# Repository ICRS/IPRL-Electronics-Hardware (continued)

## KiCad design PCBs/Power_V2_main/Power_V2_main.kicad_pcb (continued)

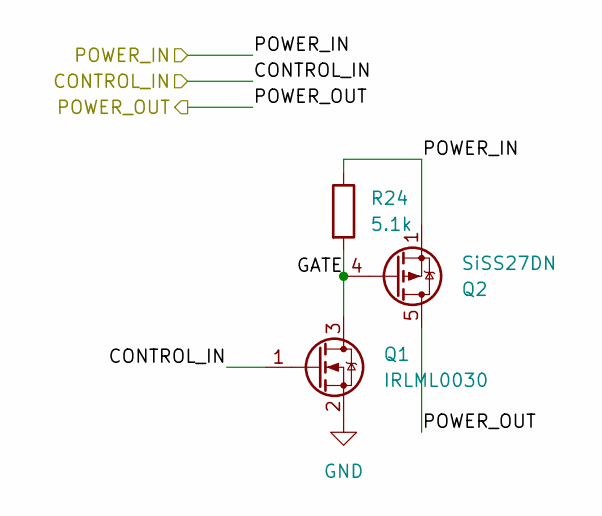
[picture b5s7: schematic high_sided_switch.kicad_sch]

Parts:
Q1: IRLML0030; SOT-23
Q2: SiSS27DN; Vishay_PowerPAK_1212-8_Single
R24: 5.1k; R_0805_2012Metric

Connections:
/14V8_PROTECTED: Q2.1 (S), Q2.2 (S), Q2.3 (S), R24.1; also elsewhere on the board
/Control/IND_GREEN: Q1.1 (G); also elsewhere on the board
/LED Indicators/GREEN_OUT: Q2.5 (D); also elsewhere on the board
/LED Indicators/Green switch/GATE: Q1.3 (D), Q2.4 (G), R24.2
GND: Q1.2 (S); also elsewhere on the board

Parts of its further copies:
Q4, Q7: SiSS27DN; Vishay_PowerPAK_1212-8_Single
Q5, Q6: IRLML0030; SOT-23
R18, R19: 5.1k; R_0805_2012Metric

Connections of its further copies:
/14V8_PROTECTED: Q4.1 (S), Q4.2 (S), Q4.3 (S), Q7.1 (S), Q7.2 (S), Q7.3 (S), R18.1, R19.1; also elsewhere on the board
/Control/IND_SIREN: Q6.1 (G); also elsewhere on the board
/Control/IND_YELLOW: Q5.1 (G); also elsewhere on the board
/LED Indicators/SIREN_OUT: Q7.5 (D); also elsewhere on the board
/LED Indicators/Siren switch/GATE: Q6.3 (D), Q7.4 (G), R19.2
/LED Indicators/YELLOW_OUT: Q4.5 (D); also elsewhere on the board
/LED Indicators/Yellow switch/GATE: Q4.4 (G), Q5.3 (D), R18.2
GND: Q5.2 (S), Q6.2 (S); also elsewhere on the board

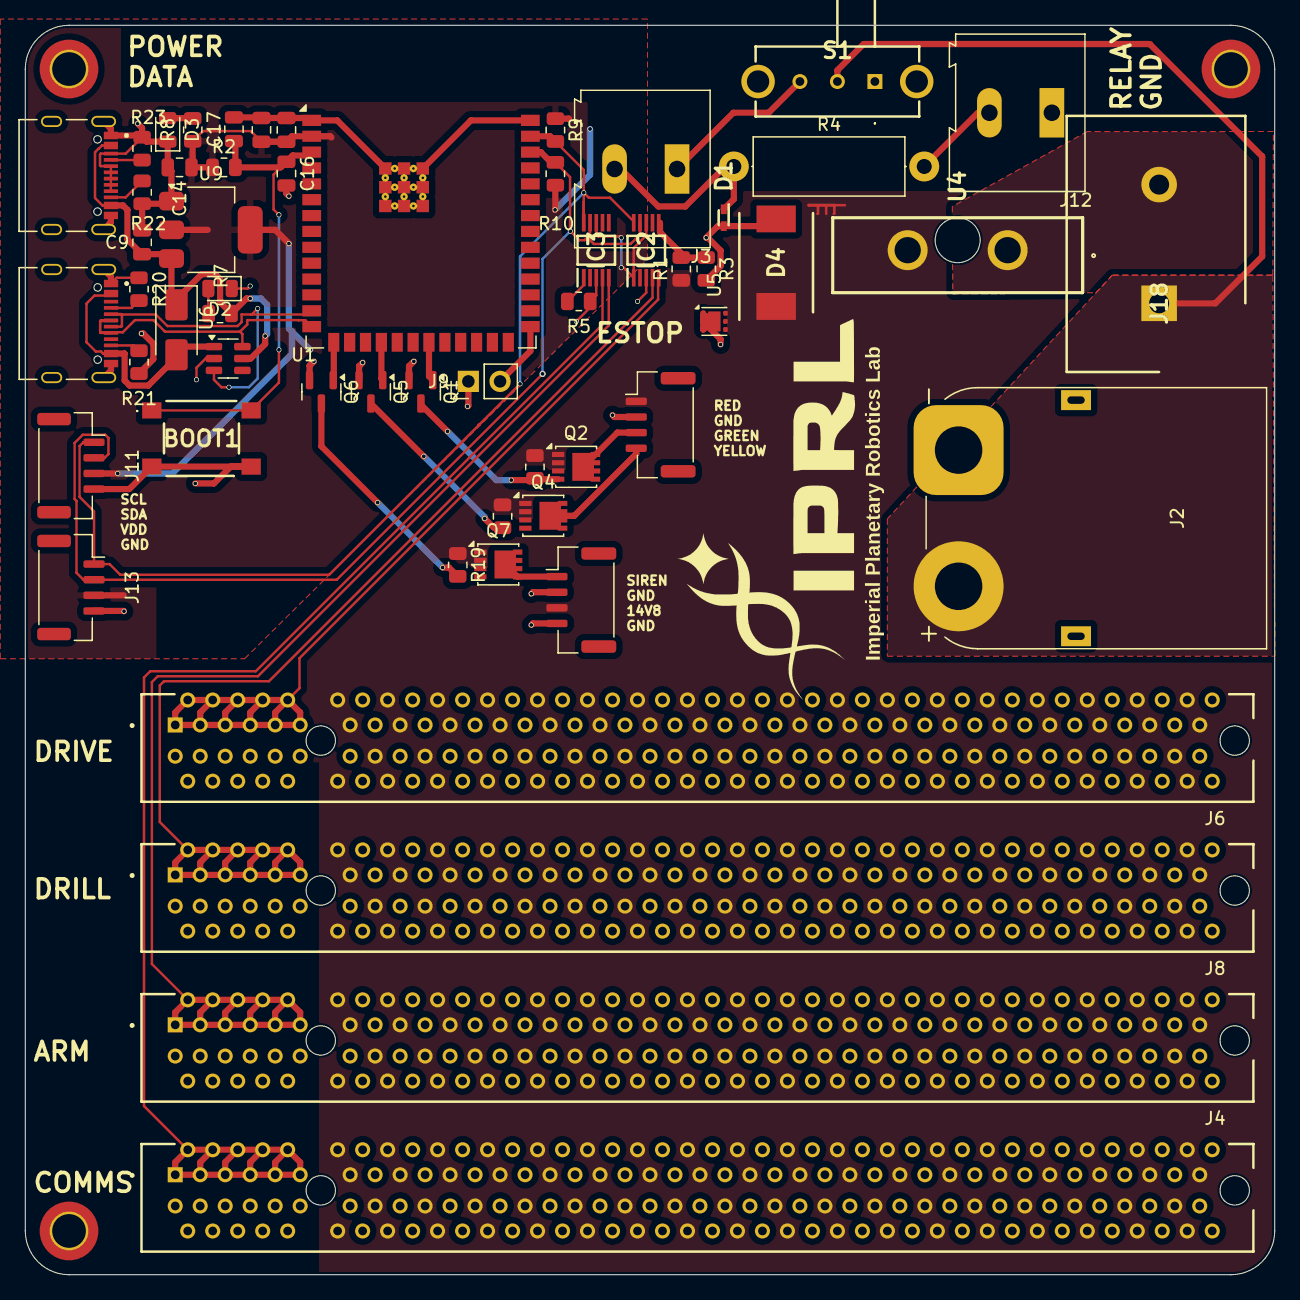
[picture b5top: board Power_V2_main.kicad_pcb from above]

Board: 2 copper layers, 100.0 x 100.0 mm, 60 parts (0 on the bottom side), 37 nets.

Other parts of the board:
J14: Conn_01x04; JST_GH_BM04B-GHS-TBT_1x04-1MP_P1.25mm_Vertical

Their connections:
/14V8_PROTECTED: J14.3; also elsewhere on the board
/LED Indicators/SIREN_OUT: J14.1; also elsewhere on the board
GND: J14.2, J14.4; also elsewhere on the board

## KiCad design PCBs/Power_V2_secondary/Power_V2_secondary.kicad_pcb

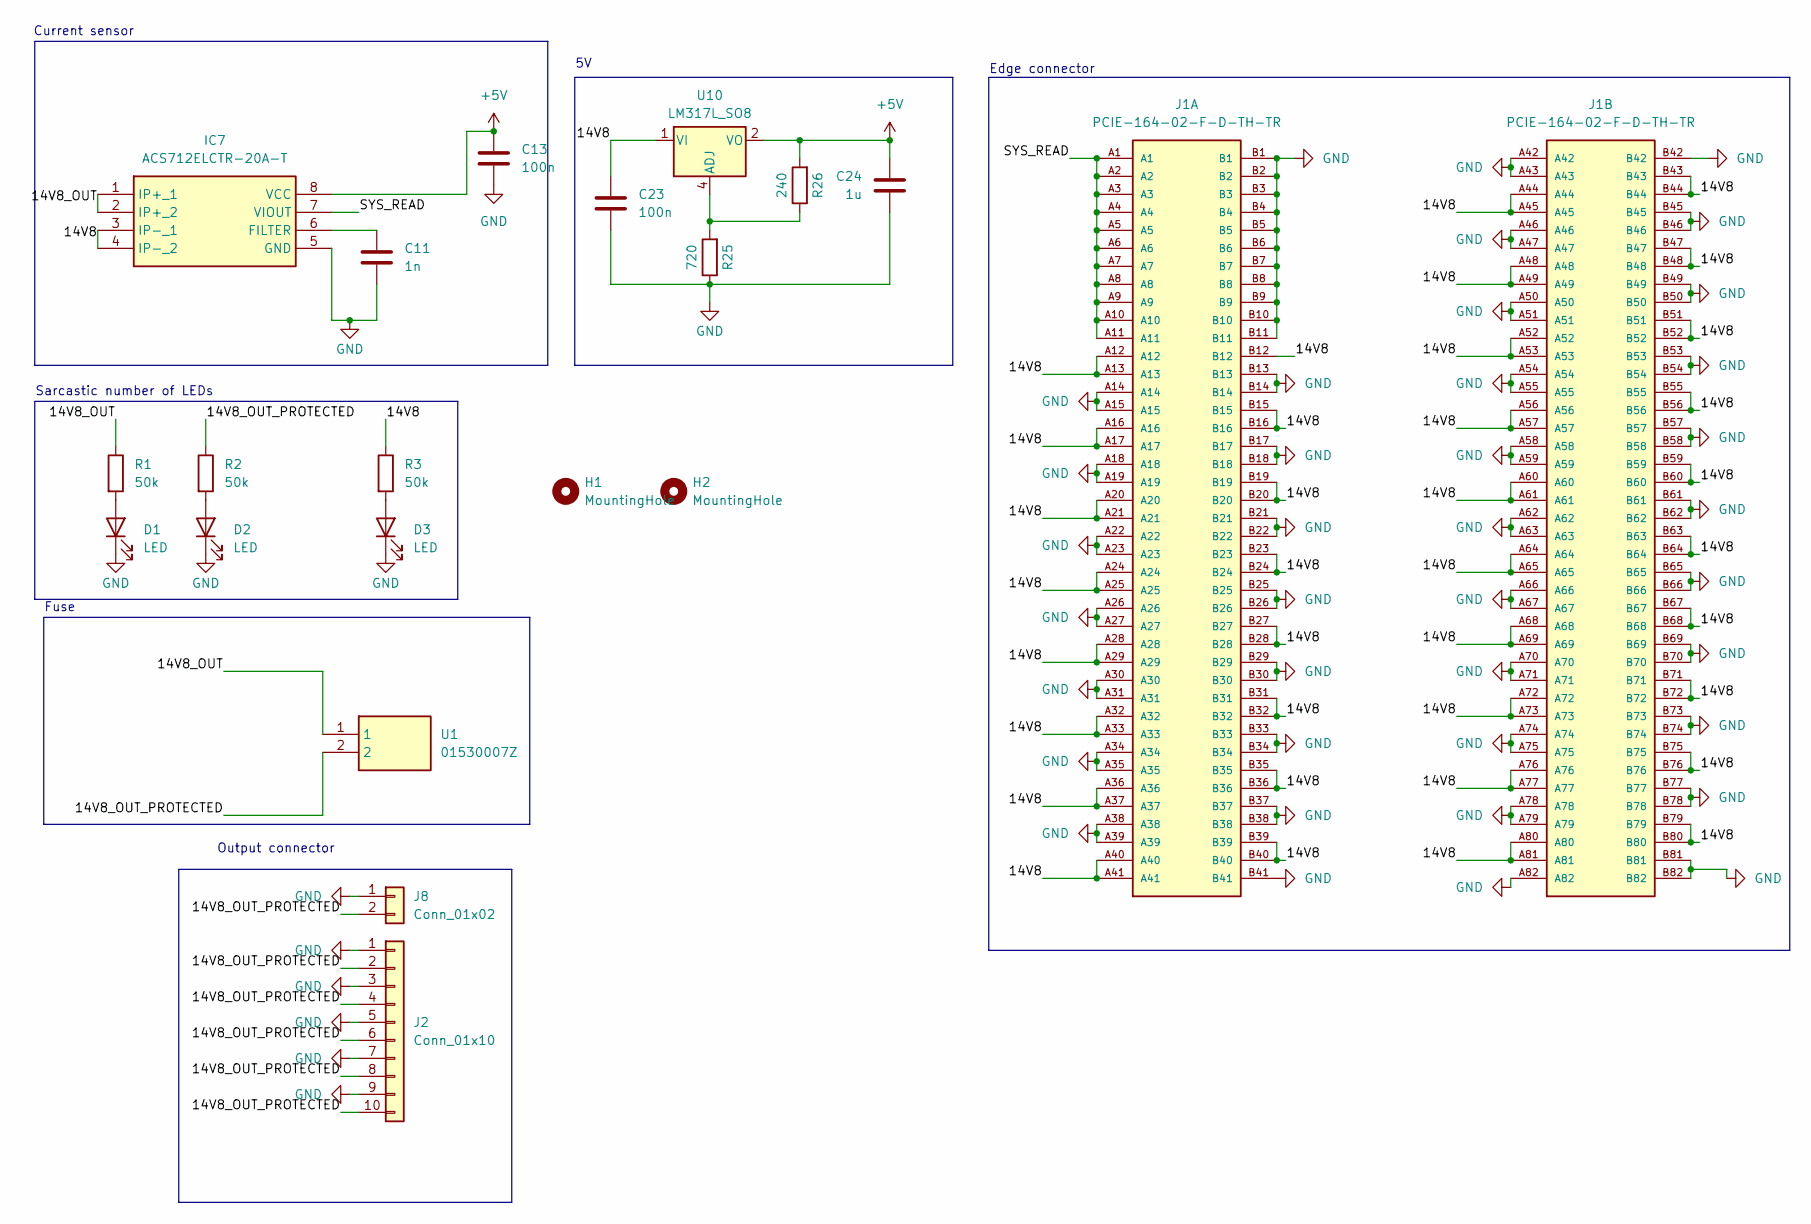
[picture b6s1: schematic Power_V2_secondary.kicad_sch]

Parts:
C11: 1n; C_0805_2012Metric
C13, C23: 100n; C_0805_2012Metric
C24: 1u; C_0805_2012Metric
D1, D2, D3: LED; D_0805_2012Metric
H1, H2: MountingHole; MountingHole_2.7mm_M2.5_DIN965_Pad_TopBottom
IC7: ACS712ELCTR-20A-T; SOIC127P600X175-8N; Manufacturer_Part_Number ACS712ELCTR-20A-T
J1: PCIE-164-02-F-D-TH-TR; BUS_PCIexpress_x16; PARTREV Y
J2: Conn_01x10; TerminalBlock_MaiXu_MX126-5.0-10P_1x10_P5.00mm
J8: Conn_01x02; AMASS_XT60PW-F_1x02_P7.20mm_Horizontal
R1, R2, R3: 50k; R_0805_2012Metric
R25: 720; R_0805_2012Metric
R26: 240; R_0805_2012Metric
U1: 01530007Z; Manufacturer_Part_Number 01530007Z; Mouser Part Number 576-01530007Z
U10: LM317L_SO8; SOIC-8_3.9x4.9mm_P1.27mm

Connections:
+5V: C13.1, C24.1, IC7.8 (VCC), R26.2, U10.2 (VO), U10.3 (VO), U10.6 (VO), U10.7 (VO)
/14V8: C23.1, IC7.3 (IP-_1), IC7.4 (IP-_2), J1.A12, J1.A13, J1.A16, J1.A17, J1.A20, J1.A21, J1.A24, J1.A25, J1.A28, J1.A29, J1.A32, J1.A33, J1.A36, J1.A37, J1.A40, J1.A41, J1.A44, J1.A45, J1.A48, J1.A49, J1.A52, J1.A53, J1.A56, J1.A57, J1.A60, J1.A61, J1.A64, J1.A65, J1.A68, J1.A69, J1.A72, J1.A73, J1.A76, J1.A77, J1.A80, J1.A81, J1.B12, J1.B15, J1.B16, J1.B19, J1.B20, J1.B23, J1.B24, J1.B27, J1.B28, J1.B31, J1.B32, J1.B35, J1.B36, J1.B39, J1.B40, J1.B43, J1.B44, J1.B47, J1.B48, J1.B51, J1.B52, J1.B55, J1.B56, J1.B59, J1.B60, J1.B63, J1.B64, J1.B67, J1.B68, J1.B71, J1.B72, J1.B75, J1.B76, J1.B79, J1.B80, R3.1, U10.1 (VI)
/14V8_OUT: IC7.1 (IP+_1), IC7.2 (IP+_2), R1.1, U1.1
/14V8_OUT_PROTECTED: J2.2, J2.4, J2.6, J2.8, J2.10, J8.2, R2.1, U1.2
/SYS_READ: IC7.7 (VIOUT), J1.A1, J1.A2, J1.A3, J1.A4, J1.A5, J1.A6, J1.A7, J1.A8, J1.A9, J1.A10, J1.A11
GND: C11.2, C13.2, C23.2, C24.2, D1.1 (K), D2.1 (K), D3.1 (K), IC7.5 (GND), J1.A14, J1.A15, J1.A18, J1.A19, J1.A22, J1.A23, J1.A26, J1.A27, J1.A30, J1.A31, J1.A34, J1.A35, J1.A38, J1.A39, J1.A42, J1.A43, J1.A46, J1.A47, J1.A50, J1.A51, J1.A54, J1.A55, J1.A58, J1.A59, J1.A62, J1.A63, J1.A66, J1.A67, J1.A70, J1.A71, J1.A74, J1.A75, J1.A78, J1.A79, J1.A82, J1.B1, J1.B2, J1.B3, J1.B4, J1.B5, J1.B6, J1.B7, J1.B8, J1.B9, J1.B10, J1.B11, J1.B13, J1.B14, J1.B17, J1.B18, J1.B21, J1.B22, J1.B25, J1.B26, J1.B29, J1.B30, J1.B33, J1.B34, J1.B37, J1.B38, J1.B41, J1.B42, J1.B45, J1.B46, J1.B49, J1.B50, J1.B53, J1.B54, J1.B57, J1.B58, J1.B61, J1.B62, J1.B65, J1.B66, J1.B69, J1.B70, J1.B73, J1.B74, J1.B77, J1.B78, J1.B81, J1.B82, J2.1, J2.3, J2.5, J2.7, J2.9, J8.1, R25.1
unnamed: D1.2 (A), R1.2
unnamed: D2.2 (A), R2.2
unnamed: D3.2 (A), R3.2
unnamed: C11.1, IC7.6 (FILTER)
unnamed: R25.2, R26.1, U10.4 (ADJ)

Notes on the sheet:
Output connector
Sarcastic number of LEDs
Edge connector
Current sensor
Fuse

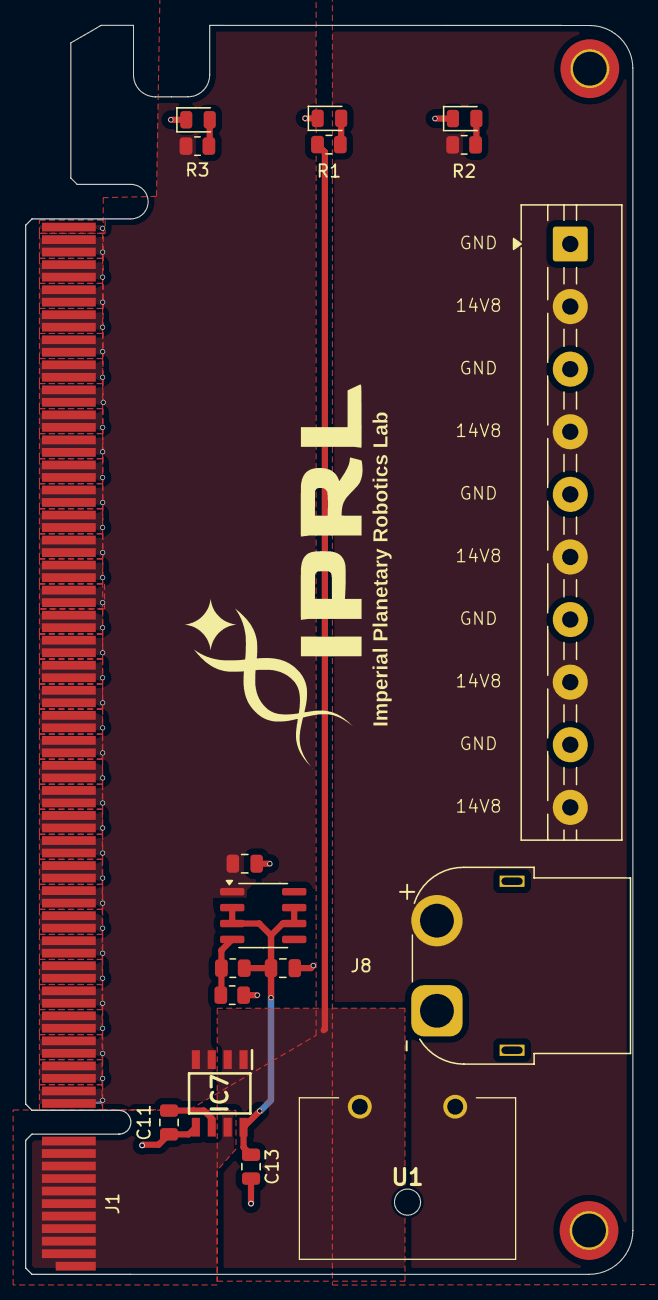
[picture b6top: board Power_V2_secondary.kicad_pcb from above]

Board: 2 copper layers, 48.5 x 99.8 mm, 20 parts (1 on the bottom side), 11 nets.

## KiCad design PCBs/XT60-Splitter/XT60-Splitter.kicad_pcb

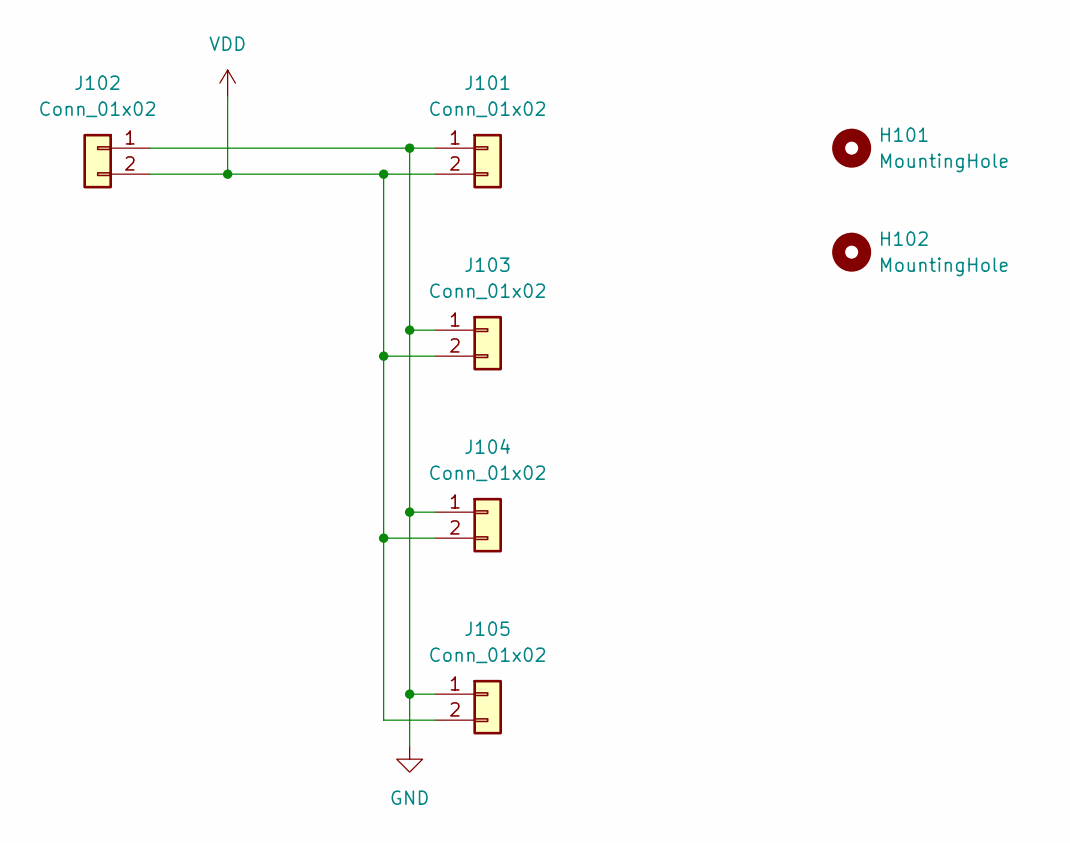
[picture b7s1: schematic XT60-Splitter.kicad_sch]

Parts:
H101, H102: MountingHole; MountingHole_3.2mm_M3_Pad
J101, J103, J104, J105: Conn_01x02; AMASS_XT60-F_1x02_P7.20mm_Vertical
J102: Conn_01x02; AMASS_XT60-M_1x02_P7.20mm_Vertical

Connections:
GND: J101.1, J102.1, J103.1, J104.1, J105.1
VDD: J101.2, J102.2, J103.2, J104.2, J105.2

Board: 2 copper layers, 7 parts (0 on the bottom side), 2 nets, no tracks yet.
